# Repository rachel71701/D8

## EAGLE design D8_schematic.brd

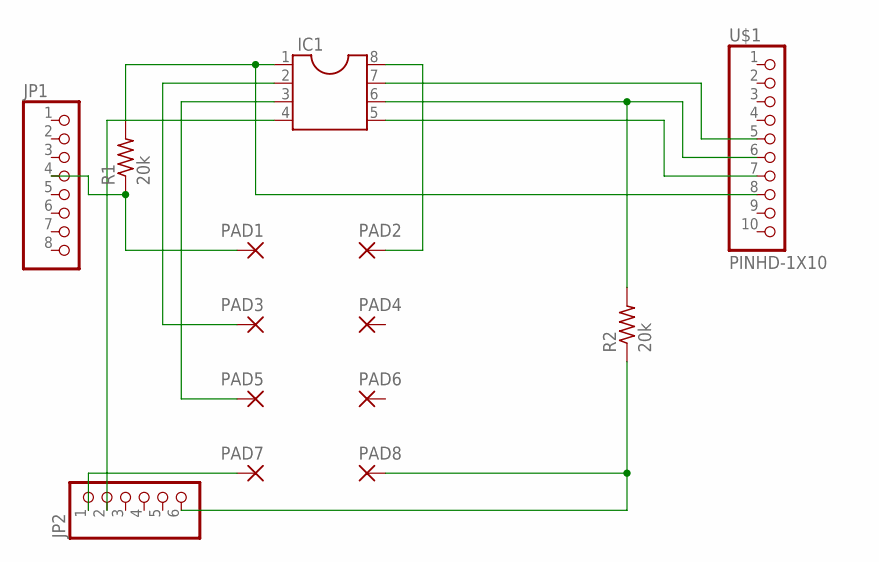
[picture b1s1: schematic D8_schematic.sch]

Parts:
IC1: DIL8S; SOCKET-08
JP1: PINHD-1X8-3.5MM; 1X08-3.5MM
JP2: PINHD-1X6-3.5MM; 1X06-3.5MM
PAD1, PAD2, PAD3, PAD4, PAD5, PAD6, PAD7, PAD8: 1,6/0,8
R1, R2: 20k; 0309/10
U$1: PINHD-1X10; 1X10-BIG

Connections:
unnamed: IC1.8, PAD2.1
unnamed: IC1.6, R2.2, U$1.6
unnamed: IC1.5, U$1.7
unnamed: IC1.7, U$1.5
unnamed: IC1.2, PAD3.1
unnamed: IC1.3, PAD5.1
unnamed: JP2.6, PAD8.1, R2.1
unnamed: JP2.1, PAD7.1
unnamed: IC1.4, JP2.2
unnamed: IC1.1, R1.2, U$1.8
unnamed: JP1.4, PAD1.1, R1.1

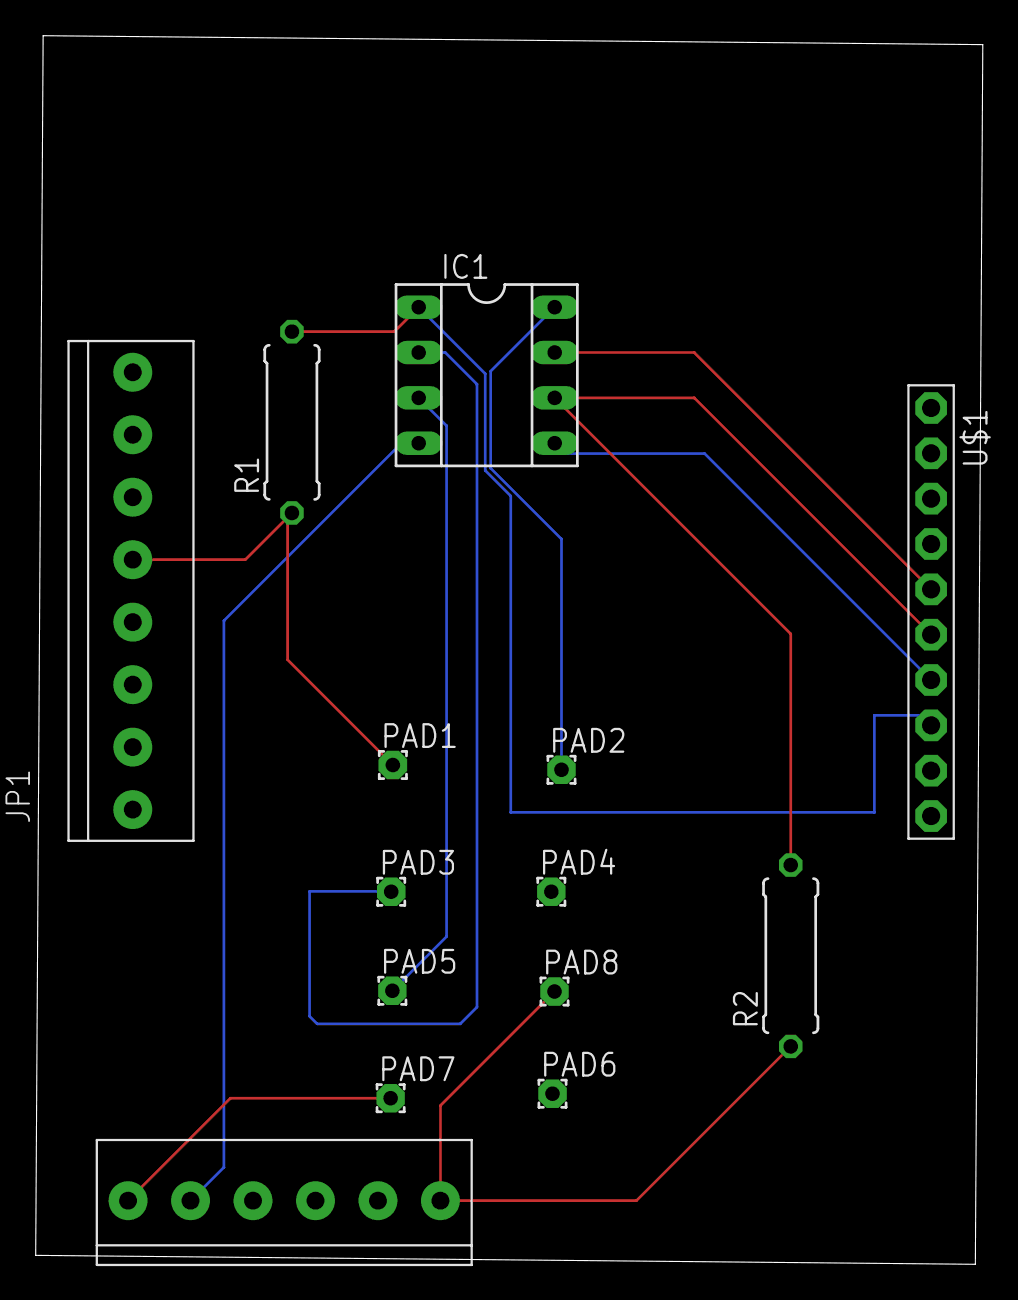
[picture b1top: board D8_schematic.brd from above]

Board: 2 copper layers, 53.1 x 68.8 mm, 14 parts (0 on the bottom side), 11 nets.
